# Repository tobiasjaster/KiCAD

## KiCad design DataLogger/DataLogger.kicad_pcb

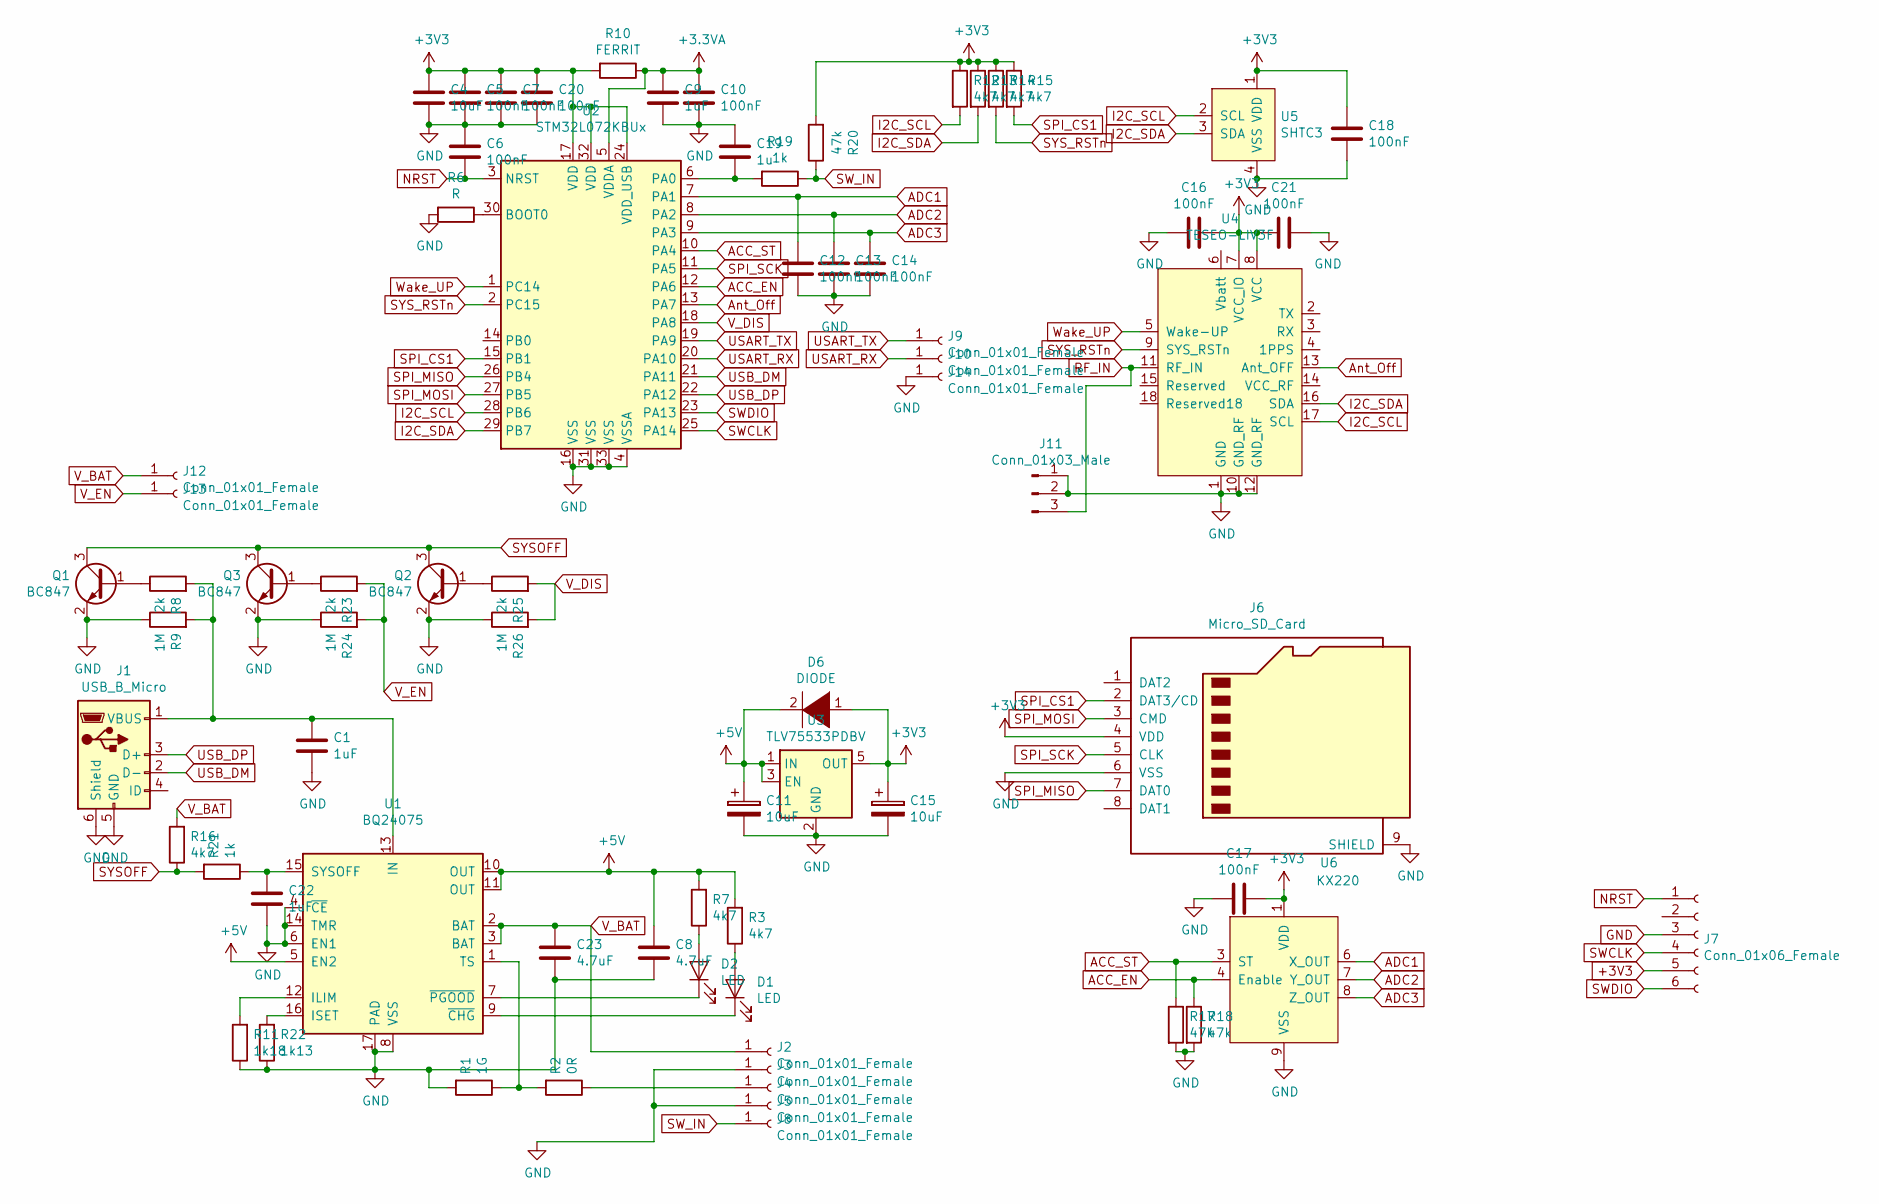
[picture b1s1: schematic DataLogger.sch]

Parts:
C1: 1uF; C_1206_3216Metric
C4: 10uF; C_0805_2012Metric
C5, C6, C7, C10, C12, C13, C14, C16, C17, C18, C20, C21: 100nF; C_0603_1608Metric
C8, C23: 4.7uF; C_1206_3216Metric
C9, C22: 1uF; C_0603_1608Metric
C11, C15: 10uF; C_1206_3216Metric
C19: 1u; C_0603_1608Metric
D1, D2: LED; LED_0603_1608Metric
D6: DIODE; D_SOD-323
J1: USB_B_Micro; USB_Micro-B_Molex_47346-0001
J2, J3, J4, J5, J8, J9, J10, J12, J13, J14: Conn_01x01_Female; PinHeader_1x01_P2.54mm_Vertical
J6: Micro_SD_Card; MOLEX_SD_47219-001
J7: Conn_01x06_Female; JST_SH_BM06B-SRSS-TB_1x06-1MP_P1.00mm_Vertical
J11: Conn_01x03_Male; CONUFL001-SMD
Q1, Q2, Q3: BC847; SOT-23
R1: 1G; R_0603_1608Metric
R2: 0R; R_0603_1608Metric
R3, R7, R12, R13, R14, R15, R16: 4k7; R_0603_1608Metric
R6: R; R_0603_1608Metric
R8, R23, R25: 2k; R_0603_1608Metric
R9, R24, R26: 1M; R_0603_1608Metric
R10: FERRIT; R_0603_1608Metric
R11: 1k18; R_0603_1608Metric
R17, R18, R20: 47k; R_0603_1608Metric
R19, R21: 1k; R_0603_1608Metric
R22: 1k13; R_0603_1608Metric
U1: BQ24075; UQFN-16-1EP_3x3mm_P0.5mm_EP1.75x1.75mm
U2: STM32L072KBUx; QFN-32-1EP_5x5mm_P0.5mm_EP3.45x3.45mm
U3: TLV75533PDBV; SOT-23-5
U4: TESEO-LIV3F; Teseo-LIV3F
U5: SHTC3
U6: KX220; KX220-1071

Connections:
+3.3VA: C9.1, C10.1, R10.1, U2.5 (VDDA)
+3V3: C4.1, C5.1, C7.1, C15.1, C16.2, C17.2, C18.1, C20.1, C21.2, D6.1 (K), J6.4 (VDD), J7.5, R10.2, R12.1, R13.1, R14.1, R15.1, R20.2, U2.17 (VDD), U2.24 (VDD_USB), U2.32 (VDD), U3.5 (OUT), U4.7 (VCC_IO), U4.8 (VCC), U5.1 (VDD), U6.1 (VDD)
+5V: C8.1, C11.1, D6.2 (A), R3.2, R7.2, U1.5 (EN2), U1.10 (OUT), U1.11 (OUT), U3.1 (IN), U3.3 (EN)
ACC_EN: R18.1, U2.12 (PA6), U6.4 (Enable)
ACC_ST: R17.1, U2.10 (PA4), U6.3 (ST)
ADC1: C12.1, U2.7 (PA1), U6.6 (X_OUT)
ADC2: C13.1, U2.8 (PA2), U6.7 (Y_OUT)
ADC3: C14.1, U2.9 (PA3), U6.8 (Z_OUT)
Ant_Off: U2.13 (PA7), U4.13 (Ant_OFF)
GND: C1.2, C4.2, C5.2, C6.1, C7.2, C8.2, C9.2, C10.2, C11.2, C12.2, C13.2, C14.2, C15.2, C16.1, C17.1, C18.2, C19.1, C20.2, C21.1, C22.2, C23.2, J1.5 (GND), J1.6 (Shield), J3.1, J5.1, J6.6 (VSS), J6.9 (SHIELD), J7.3, J11.1, J11.2, J14.1, Q1.2 (E), Q2.2 (E), Q3.2 (E), R1.2, R6.2, R9.1, R11.1, R17.2, R18.2, R22.1, R24.1, R26.1, U1.4 (~CE), U1.6 (EN1), U1.8 (VSS), U1.14 (TMR), U1.17 (PAD), U2.4 (VSSA), U2.16 (VSS), U2.31 (VSS), U2.33 (VSS), U3.2 (GND), U4.1 (GND), U4.10 (GND_RF), U4.12 (GND_RF), U5.4 (VSS), U5.5 (PAD), U6.9 (VSS)
I2C_SCL: R12.2, U2.28 (PB6), U4.17 (SCL), U5.2 (SCL)
I2C_SDA: R13.2, U2.29 (PB7), U4.16 (SDA), U5.3 (SDA)
NRST: C6.2, J7.1, U2.3 (NRST)
unnamed: C1.1, J1.1 (VBUS), R8.2, R9.2, U1.13 (IN)
unnamed: C19.2, R19.2, U2.6 (PA0)
unnamed: C22.1, R21.1, U1.15 (SYSOFF)
unnamed: D1.1 (K), U1.9 (~CHG)
unnamed: D1.2 (A), R3.1
unnamed: D2.1 (K), U1.7 (~PGOOD)
unnamed: D2.2 (A), R7.1
unnamed: J4.1, R2.1
unnamed: Q1.1 (B), R8.1
unnamed: Q2.1 (B), R25.1
unnamed: Q3.1 (B), R23.1
unnamed: R1.1, R2.2, U1.1 (TS)
unnamed: R6.1, U2.30 (BOOT0)
unnamed: R11.2, U1.12 (ILIM)
unnamed: R22.2, U1.16 (ISET)
RF_IN: J11.3, U4.11 (RF_IN)
SPI_CS1: J6.2 (DAT3/CD), R15.2, U2.15 (PB1)
SPI_MISO: J6.7 (DAT0), U2.26 (PB4)
SPI_MOSI: J6.3 (CMD), U2.27 (PB5)
SPI_SCK: J6.5 (CLK), U2.11 (PA5)
SWCLK: J7.4, U2.25 (PA14)
SWDIO: J7.6, U2.23 (PA13)
SW_IN: J8.1, R19.1, R20.1
SYSOFF: Q1.3 (C), Q2.3 (C), Q3.3 (C), R16.1, R21.2
SYS_RSTn: R14.2, U2.2 (PC15), U4.9 (SYS_RSTn)
USART_RX: J10.1, U2.20 (PA10)
USART_TX: J9.1, U2.19 (PA9)
USB_DM: J1.2 (D-), U2.21 (PA11)
USB_DP: J1.3 (D+), U2.22 (PA12)
V_BAT: C23.1, J2.1, J12.1, R16.2, U1.2 (BAT), U1.3 (BAT)
V_DIS: R25.2, R26.2, U2.18 (PA8)
V_EN: J13.1, R23.2, R24.2
Wake_UP: U2.1 (PC14), U4.5 (Wake-UP)

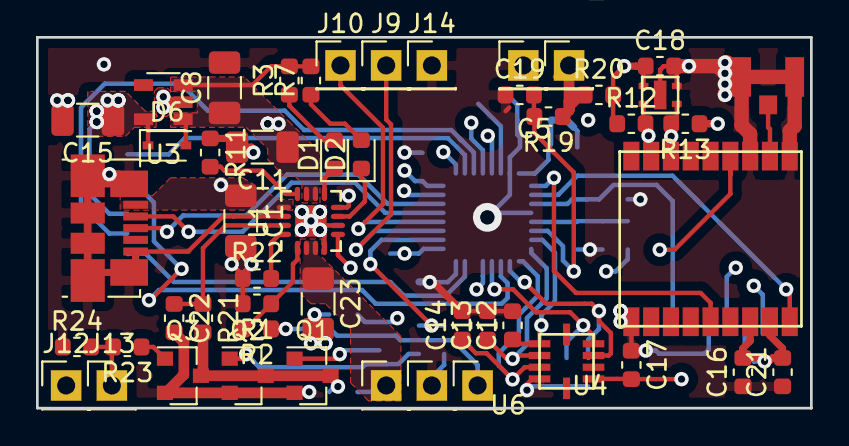
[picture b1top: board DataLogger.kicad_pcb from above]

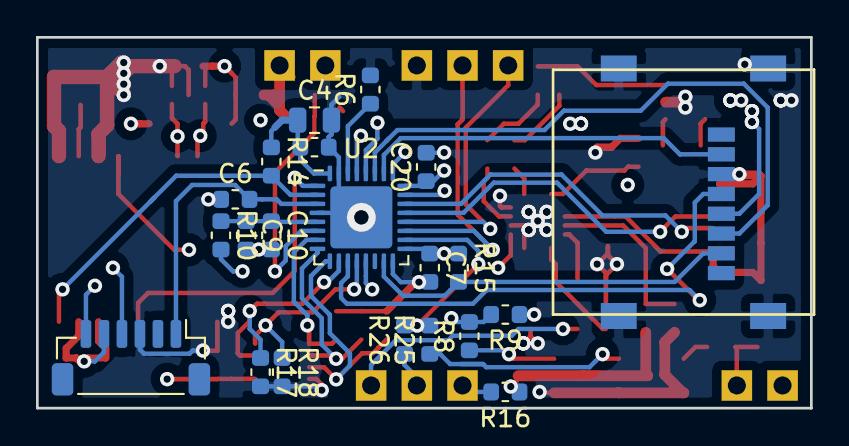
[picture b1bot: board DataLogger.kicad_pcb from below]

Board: 4 copper layers, 43.0 x 20.6 mm, 71 parts (21 on the bottom side), 46 nets.
